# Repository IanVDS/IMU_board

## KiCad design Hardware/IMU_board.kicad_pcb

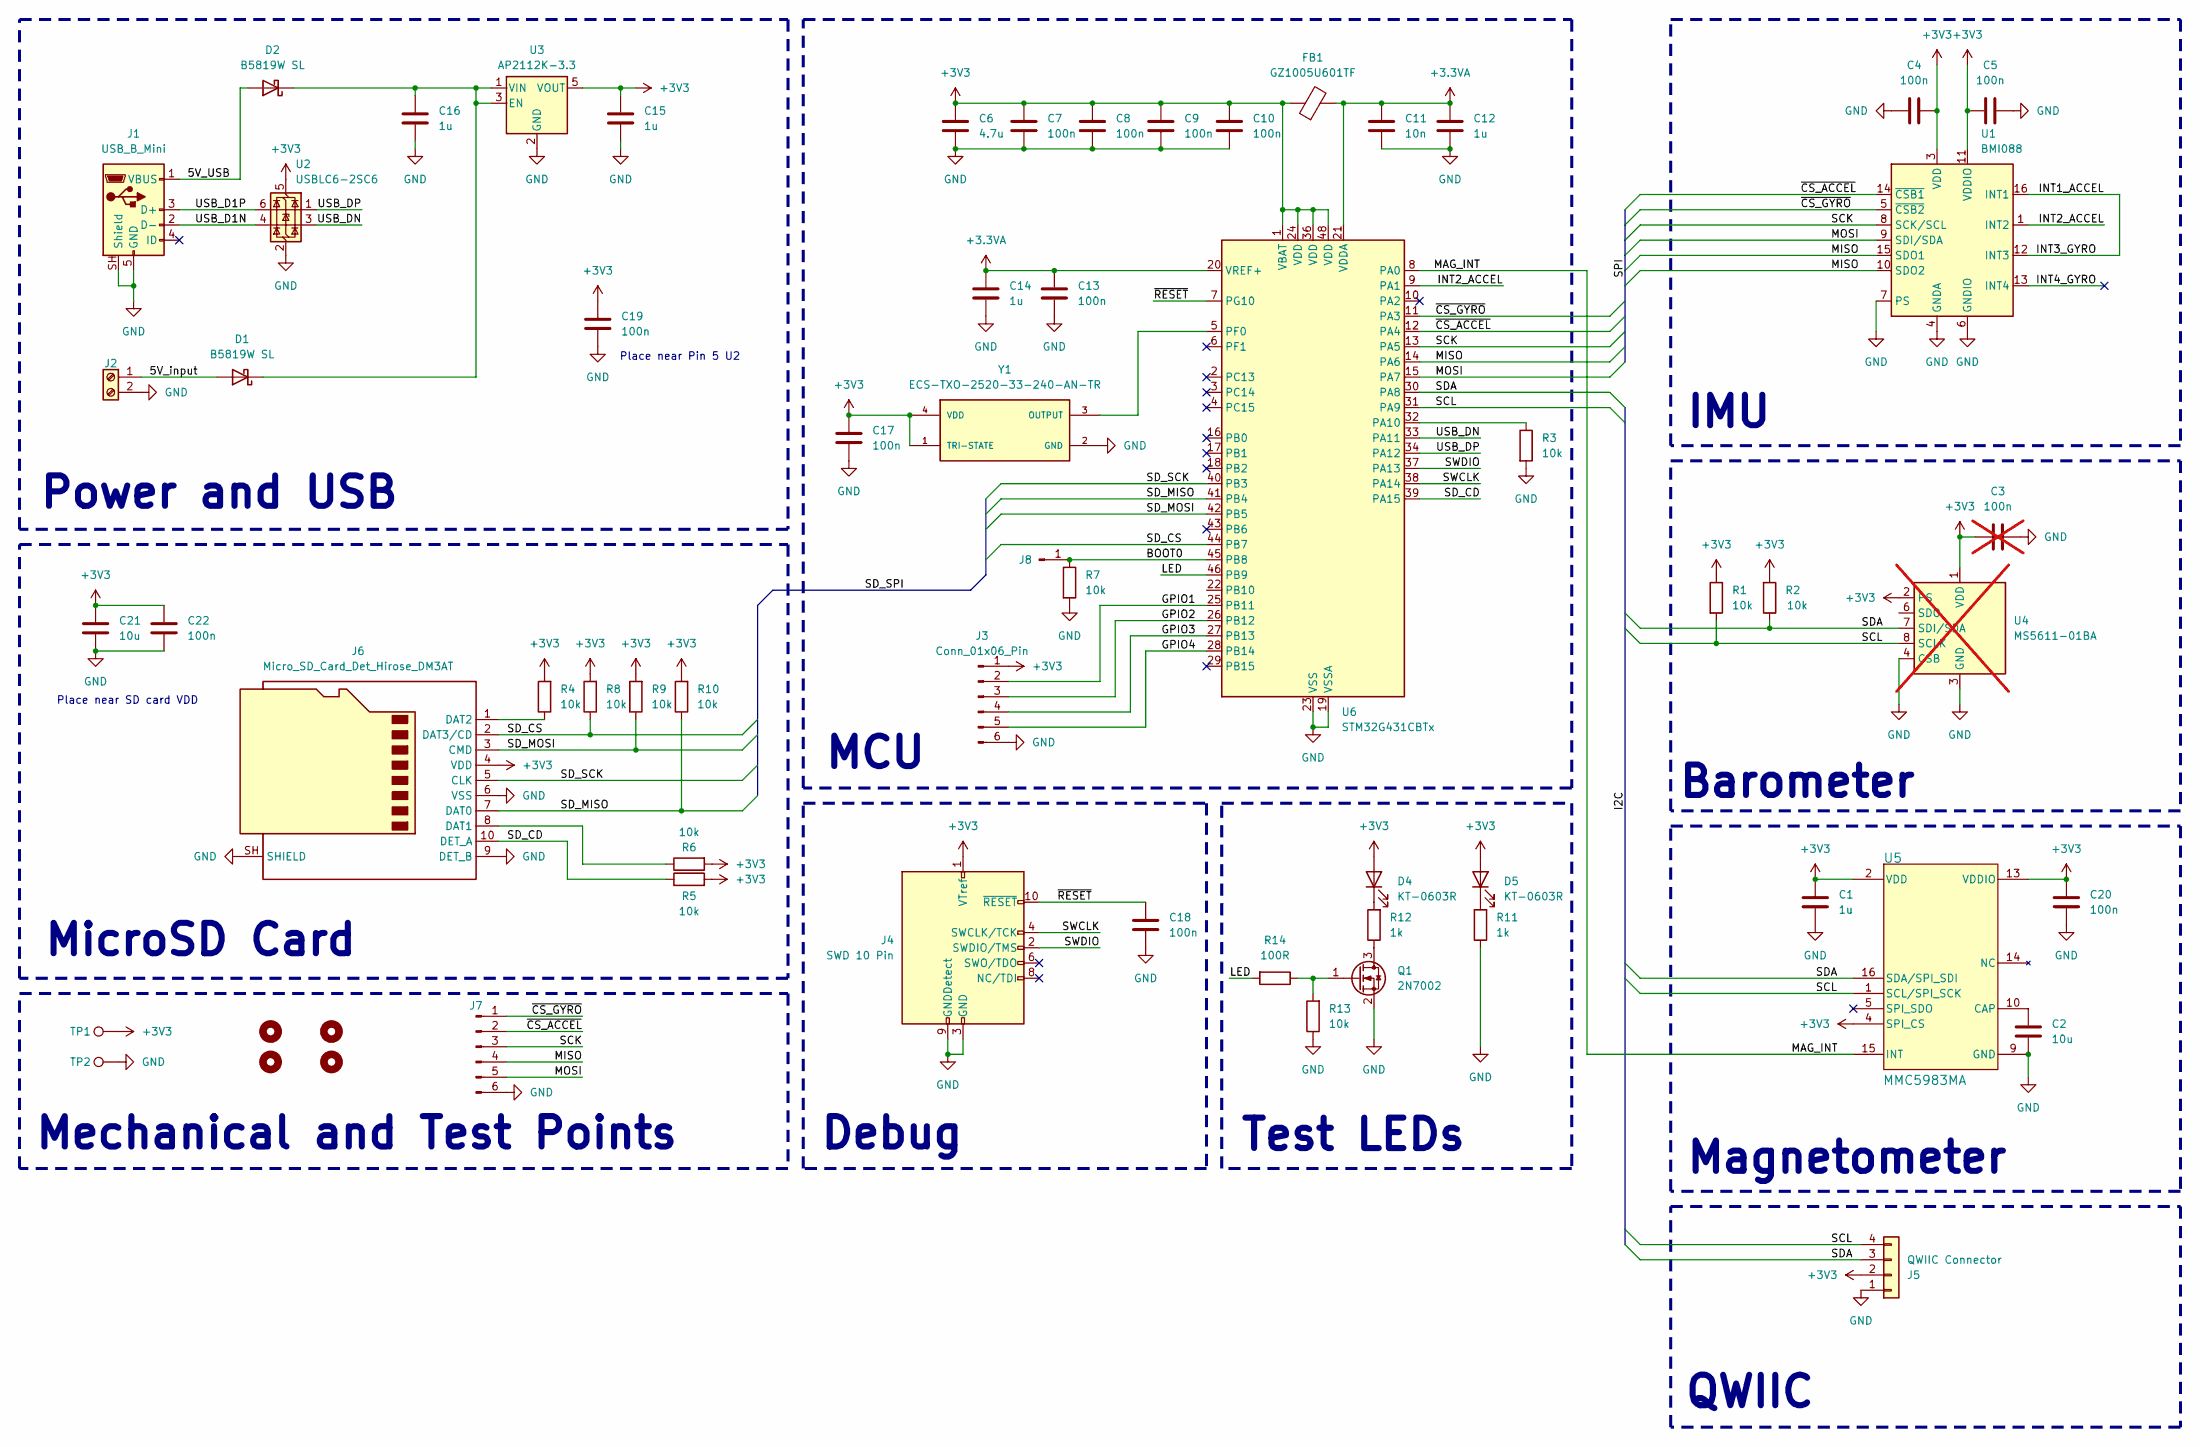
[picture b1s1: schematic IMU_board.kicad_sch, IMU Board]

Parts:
C1, C12, C14, C15, C16: 1u; C_0402_1005Metric
C2, C21: 10u; C_0402_1005Metric
C3: 100n; C_0402_1005Metric; not fitted
C4, C5, C7, C8, C9, C10, C13, C17, C18, C19, C20, C22: 100n; C_0402_1005Metric
C6: 4.7u; C_0402_1005Metric
C11: 10n; C_0402_1005Metric
D1, D2: B5819W SL; D_SOD-123
D4, D5: KT-0603R; LED_0603_1608Metric
FB1: GZ1005U601TF; L_0402_1005Metric
H1, H2, H3, H4: MountingHole; MountingHole_3.2mm_M3
J1: USB_B_Mini; CONN_SD-54819-027_MOL
J2: Screw_Terminal_01x02; TerminalBlock_Phoenix_MPT-0,5-2-2.54_1x02_P2.54mm_Horizontal
J3: Conn_01x06_Pin; PinHeader_1x06_P1.27mm_Vertical
J4: SWD 10 Pin; SAMTEC_FTSH-105-01-X-DV-K-X
J5: QWIIC Connector; JST_SH_SM04B-SRSS-TB_1x04-1MP_P1.00mm_Horizontal
J6: Micro_SD_Card_Det_Hirose_DM3AT; microSD_HC_Hirose_DM3AT-SF-PEJM5
J7: SPI; PinHeader_1x06_P1.27mm_Vertical
J8: Conn_01x01_Pin; PinHeader_1x01_P1.27mm_Vertical
Q1: 2N7002; SOT-23
R1, R2, R3, R4, R5, R6, R7, R8, R9, R10, R13: 10k; R_0402_1005Metric
R11, R12: 1k; R_0402_1005Metric
R14: 100R; R_0402_1005Metric
TP1, TP2: TestPoint; TestPoint_Pad_D1.0mm
U1: BMI088; Bosch_LGA-16_4.5x3mm_P0.5mm_LayoutBorder7x1y_ClockwisePinNu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
U2: USBLC6-2SC6; SOT-23-6
U3: AP2112K-3.3; SOT-23-5
U4: MS5611-01BA; LGA-8_3x5mm_P1.25mm; not fitted
U5: MMC5983MA; MMC5983MA_MEM
U6: STM32G431CBTx; LQFP-48_7x7mm_P0.5mm
Y1: ECS-TXO-2520-33-240-AN-TR; OSC_ECS-TXO-2520-33-240-AN-TR; MPN ECS-TXO-2520-33-240-AN-TR

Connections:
+3.3VA: C11.1, C12.1, C13.1, C14.1, FB1.2, U6.20 (VREF+), U6.21 (VDDA)
+3V3: C1.1, C3.1, C4.2, C5.1, C6.1, C7.1, C8.1, C9.1, C10.1, C15.1, C17.1, C19.1, C20.1, C21.1, C22.1, D4.2 (A), D5.2 (A), FB1.1, J3.1, J4.1 (VTref), J5.2, J6.4 (VDD), R1.1, R2.2, R4.2, R5.2, R6.2, R8.2, R9.2, R10.2, TP1.1 (1_1), U1.3 (VDD), U1.11 (VDDIO), U2.5 (VBUS), U3.5 (VOUT), U4.1 (VDD), U4.2 (PS), U5.2 (VDD), U5.4 (SPI_CS), U5.13 (VDDIO), U6.1 (VBAT), U6.24 (VDD), U6.36 (VDD), U6.48 (VDD), Y1.1 (TRI-STATE), Y1.4 (VDD)
/5V_USB: D2.2 (A), J1.1 (VBUS)
/5V_input: D1.2 (A), J2.1
/BOOT0: J8.1 (Pin_1_1), R7.1, U6.45 (PB8)
/GPIO1: J3.2, U6.25 (PB11)
/GPIO2: J3.3, U6.26 (PB12)
/GPIO3: J3.4, U6.27 (PB13)
/GPIO4: J3.5, U6.28 (PB14)
/INT1_ACCEL: U1.12 (INT3), U1.16 (INT1)
/INT2_ACCEL: U1.1 (INT2), U6.9 (PA1)
/INT4_GYRO: U1.13 (INT4)
/LED: R14.2, U6.46 (PB9)
/MAG_INT: U5.15 (INT), U6.8 (PA0)
/MISO: J7.4, U1.10 (SDO2), U1.15 (SDO1), U6.14 (PA6)
/MOSI: J7.5, U1.9 (SDI/SDA), U6.15 (PA7)
/SCK: J7.3, U1.8 (SCK/SCL), U6.13 (PA5)
/SCL: J5.4, R1.2, U4.8 (SCLK), U5.1 (SCL/SPI_SCK), U6.31 (PA9)
/SDA: J5.3, R2.1, U4.7 (SDI/SDA), U5.16 (SDA/SPI_SDI), U6.30 (PA8)
/SD_CD: J6.10 (DET_A), R5.1, U6.39 (PA15)
/SD_CS: J6.2 (DAT3/CD), R8.1, U6.44 (PB7)
/SD_MISO: J6.7 (DAT0), R10.1, U6.41 (PB4)
/SD_MOSI: J6.3 (CMD), R9.1, U6.42 (PB5)
/SD_SCK: J6.5 (CLK), U6.40 (PB3)
/SWCLK: J4.4 (SWCLK/TCK), U6.38 (PA14)
/SWDIO: J4.2 (SWDIO/TMS), U6.37 (PA13)
/USB_D1N: J1.2 (D-), U2.4 (I/O2)
/USB_D1P: J1.3 (D+), U2.6 (I/O1)
/USB_DN: U2.3 (I/O2), U6.33 (PA11)
/USB_DP: U2.1 (I/O1), U6.34 (PA12)
/~CS_ACCEL: J7.2, U1.14 (~CSB1), U6.12 (PA4)
/~CS_GYRO: J7.1, U1.5 (~CSB2), U6.11 (PA3)
/~RESET: C18.1, J4.10 (~RESET), U6.7 (PG10)
GND: C1.2, C2.2, C3.2, C4.1, C5.2, C6.2, C7.2, C8.2, C9.2, C10.2, C11.2, C12.2, C13.2, C14.2, C15.2, C16.2, C17.2, C18.2, C19.2, C20.2, C21.2, C22.2, J1.5 (GND), J1.SH (Shield), J2.2, J3.6, J4.3 (GND), J4.5 (GND), J4.9 (GNDDetect), J5.1, J6.6 (VSS), J6.9 (DET_B), J6.SH (SHIELD), J7.6, Q1.2 (S), R3.2, R7.2, R11.1, R13.1, TP2.1 (1_1), U1.2 (GNDA), U1.4 (GNDA), U1.6 (GNDIO), U1.7 (PS), U2.2 (GND), U3.2 (GND), U4.3 (GND), U4.4 (CSB), U4.5 (CSB), U5.9 (GND), U5.11 (GND), U6.19 (VSSA), U6.23 (VSS), U6.35 (VSS), U6.47 (VSS), Y1.2 (GND)
unnamed: C16.1, D1.1 (K), D2.1 (K), U3.1 (VIN), U3.3 (EN)
unnamed: D4.1 (K), R12.2
unnamed: D5.1 (K), R11.2
unnamed: J6.8 (DAT1), R6.1
unnamed: J6.1 (DAT2), R4.1
unnamed: Q1.3 (D), R12.1
unnamed: Q1.1 (G), R13.2, R14.1
unnamed: C2.1, U5.10 (CAP)
unnamed: R3.1, U6.32 (PA10)
unnamed: U6.5 (PF0), Y1.3 (OUTPUT)

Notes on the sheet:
Mechanical and Test Points
Debug
Magnetometer
Place near SD card VDD
Test LEDs
MCU
IMU
MicroSD Card
Power and USB
Place near Pin 5 U2
Barometer
QWIIC

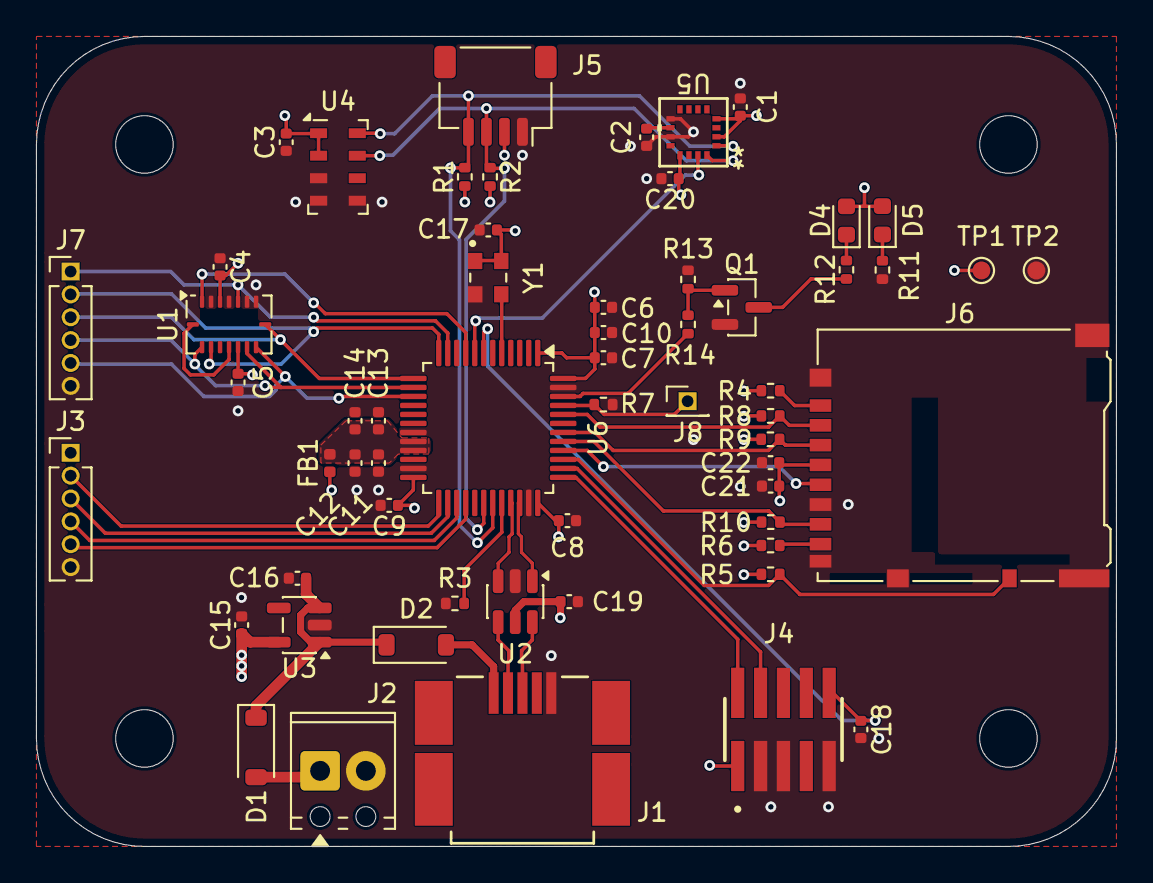
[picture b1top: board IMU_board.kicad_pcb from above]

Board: 4 copper layers, 60.0 x 45.0 mm, 63 parts (0 on the bottom side), 43 nets.

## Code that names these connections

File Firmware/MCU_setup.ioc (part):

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Mcu.Name=STM32G431C(6-8-B)Tx
Mcu.Package=LQFP48
Mcu.UserName=STM32G431CBTx
PA0.Signal=S_TIM2_CH1
PA1.Signal=S_TIM2_CH2
PA11.Mode=Device
PA11.Signal=USB_DM
PA12.Mode=Device
PA12.Signal=USB_DP
PA13.Mode=Serial_Wire
PA13.Signal=SYS_JTMS-SWDIO
PA14.Mode=Serial_Wire
PA14.Signal=SYS_JTCK-SWCLK
PA15.Signal=GPIO_Input
PA3.Signal=GPIO_Output
PA4.Signal=GPIO_Output
PA5.Mode=Full_Duplex_Master
PA5.Signal=SPI1_SCK
PA6.Mode=Full_Duplex_Master
PA6.Signal=SPI1_MISO
PA7.Mode=Full_Duplex_Master
PA7.Signal=SPI1_MOSI
PA8.Mode=I2C
PA8.Signal=I2C2_SDA
PA9.Mode=I2C
PA9.Signal=I2C2_SCL
PB3.Mode=Full_Duplex_Master
PB3.Signal=SPI3_SCK
PB4.Mode=Full_Duplex_Master
PB4.Signal=SPI3_MISO
PB5.Mode=Full_Duplex_Master
PB5.Signal=SPI3_MOSI
PB7.Signal=GPIO_Output
PB9.Signal=GPIO_Output
PF0-OSC_IN.Mode=HSE-External-Clock-Source
PF0-OSC_IN.Signal=RCC_OSC_IN
RCC.HSE_VALUE=8000000
RCC.SYSCLKFreq_VALUE=16000000
board=custom
